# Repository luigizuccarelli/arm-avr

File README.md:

# arm-avr

## Arm 0 based on the LPC11U37FBD64-501 32bit mcu

 * **Design**
   * All pcb and schematics are in Kicad format
   * Double sided through hole plated pcb
   * Not in production yet waiting for pcb's to be manufactured for QA testing

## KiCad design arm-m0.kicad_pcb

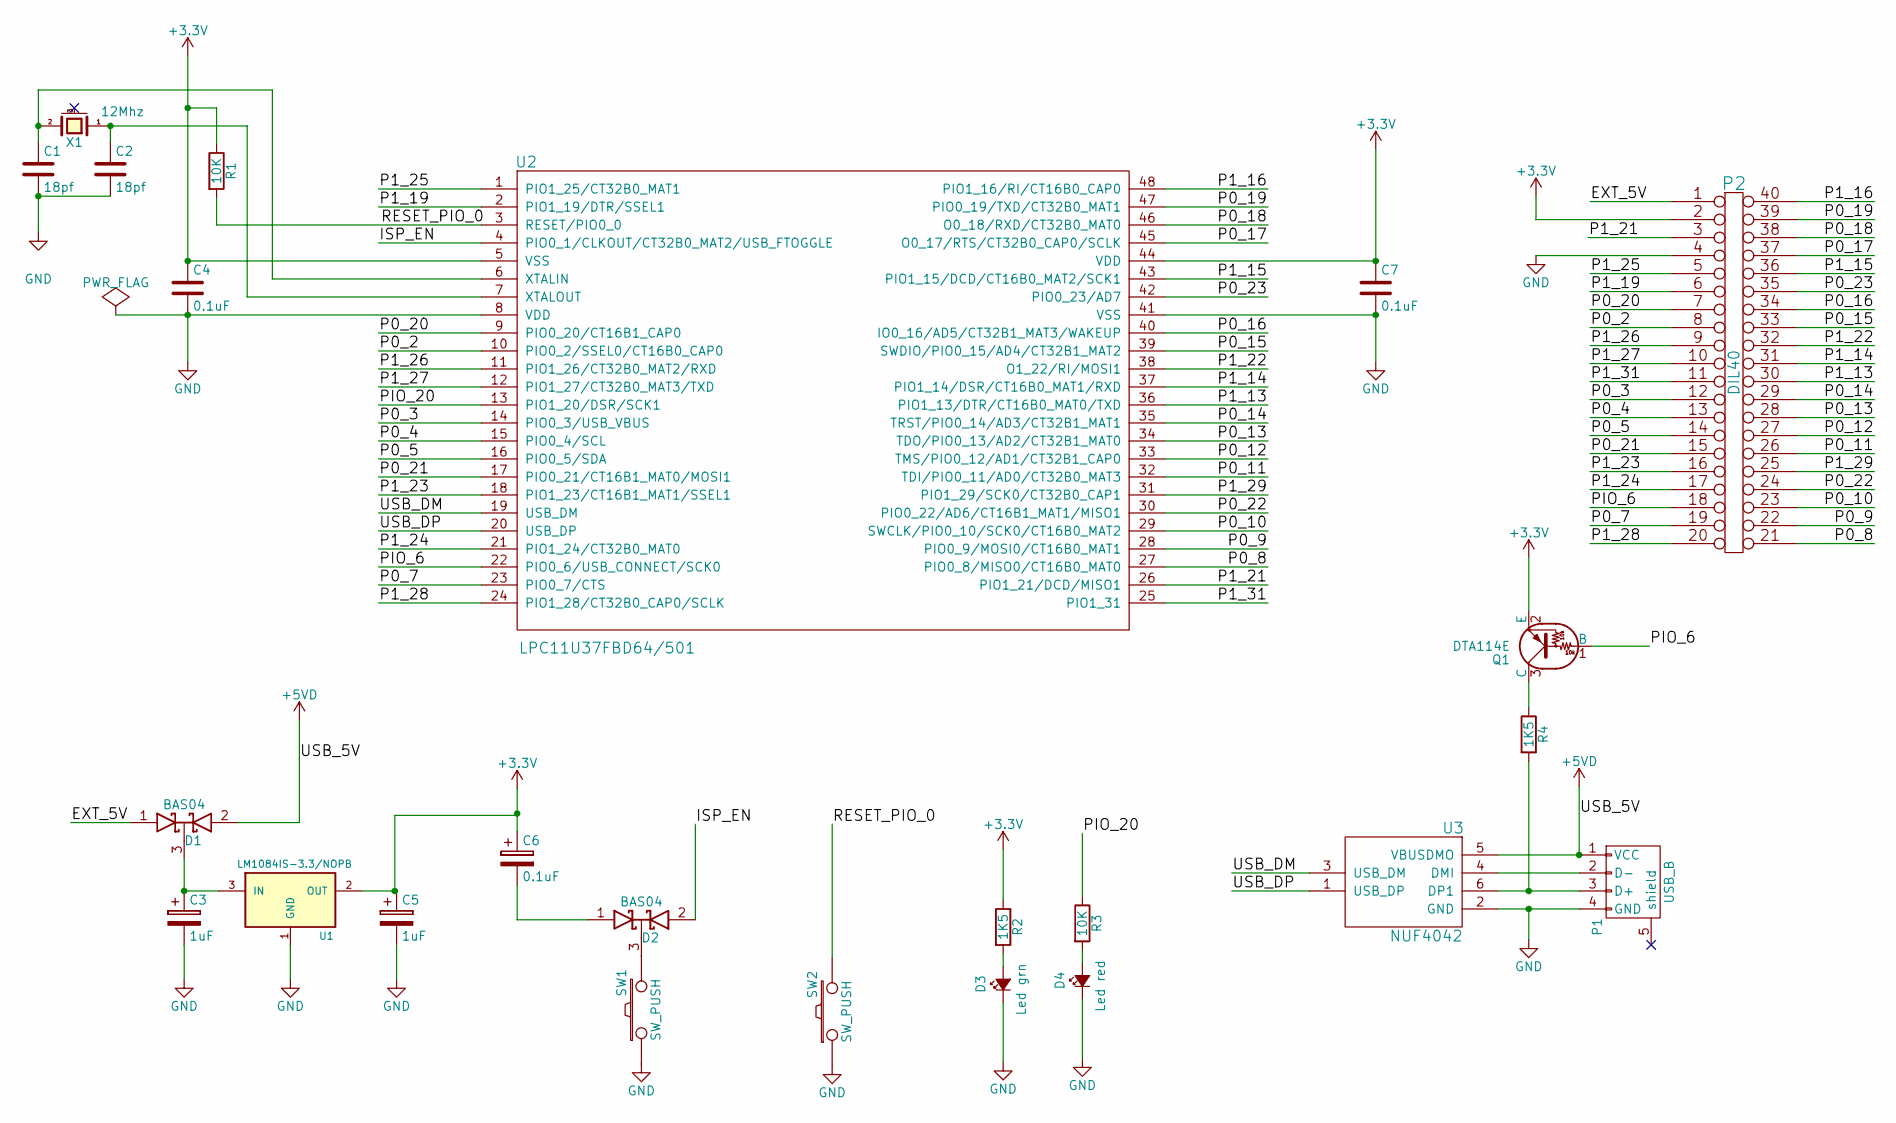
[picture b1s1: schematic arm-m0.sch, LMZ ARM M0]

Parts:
C1, C2: 18pf; C_0402
C3, C5: 1uF; R_0603_HandSoldering
C4, C6, C7: 0.1uF; R_0603_HandSoldering
D1, D2: BAS04; SOT-23
D3: Led grn; LED-0805
D4: Led red; LED-0805
P1: USB_B; USB_Micro-B
P2: DIL40; DIP-40_W25.4mm
Q1: DTA114E; SOT-23
R1: 10K; R_0603
R2, R4: 1K5; R_0603_HandSoldering
R3: 10K; R_0603_HandSoldering
SW1, SW2: SW_PUSH; SW_PUSH_SMALL
U1: LM1084IS-3.3/NOPB; SOT-23
U2: LPC11U37FBD64/501; LQFP-48_7x7mm_Pitch0.5mm
U3: NUF4042; SOT-563
X1: 12Mhz; Crystal_SMD_0603_4Pads

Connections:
+3V3: C4.1, C5.1, C6.1, C7.1, P2.2, Q1.2 (E), R1.1, R2.1, U1.2 (OUT), U2.5 (VSS), U2.44 (VDD)
+5VD: D1.2 (A), P1.1 (VCC), U3.5 (VBUSDMO)
/EXT_5V: D1.1 (A), P2.1
/ISP_EN: D2.2 (A), U2.4 (PIO0_1/CLKOUT/CT32B0_MAT2/USB_FTOGGLE)
/P0_2: P2.8, U2.10 (PIO0_2/SSEL0/CT16B0_CAP0)
/P0_3: P2.12, U2.14 (PIO0_3/USB_VBUS)
/P0_4: P2.13, U2.15 (PIO0_4/SCL)
/P0_5: P2.14, U2.16 (PIO0_5/SDA)
/P0_7: P2.19, U2.23 (PIO0_7/CTS)
/P0_8: P2.21, U2.27 (PIO0_8/MISO0/CT16B0_MAT0)
/P0_9: P2.22, U2.28 (PIO0_9/MOSI0/CT16B0_MAT1)
/P0_10: P2.23, U2.29 (SWCLK/PIO0_10/SCK0/CT16B0_MAT2)
/P0_11: P2.26, U2.32 (TDI/PIO0_11/AD0/CT32B0_MAT3)
/P0_12: P2.27, U2.33 (TMS/PIO0_12/AD1/CT32B1_CAP0)
/P0_13: P2.28, U2.34 (TDO/PIO0_13/AD2/CT32B1_MAT0)
/P0_14: P2.29, U2.35 (TRST/PIO0_14/AD3/CT32B1_MAT1)
/P0_15: P2.33, U2.39 (SWDIO/PIO0_15/AD4/CT32B1_MAT2)
/P0_16: P2.34, U2.40 (IO0_16/AD5/CT32B1_MAT3/WAKEUP)
/P0_17: P2.37, U2.45 (O0_17/RTS/CT32B0_CAP0/SCLK)
/P0_18: P2.38, U2.46 (O0_18/RXD/CT32B0_MAT0)
/P0_19: P2.39, U2.47 (PIO0_19/TXD/CT32B0_MAT1)
/P0_20: P2.7, U2.9 (PIO0_20/CT16B1_CAP0)
/P0_21: P2.15, U2.17 (PIO0_21/CT16B1_MAT0/MOSI1)
/P0_22: P2.24, U2.30 (PIO0_22/AD6/CT16B1_MAT1/MISO1)
/P0_23: P2.35, U2.42 (PIO0_23/AD7)
/P1_13: P2.30, U2.36 (PIO1_13/DTR/CT16B0_MAT0/TXD)
/P1_14: P2.31, U2.37 (PIO1_14/DSR/CT16B0_MAT1/RXD)
/P1_15: P2.36, U2.43 (PIO1_15/DCD/CT16B0_MAT2/SCK1)
/P1_16: P2.40, U2.48 (PIO1_16/RI/CT16B0_CAP0)
/P1_19: P2.6, U2.2 (PIO1_19/DTR/SSEL1)
/P1_21: P2.3, U2.26 (PIO1_21/DCD/MISO1)
/P1_22: P2.32, U2.38 (O1_22/RI/MOSI1)
/P1_23: P2.16, U2.18 (PIO1_23/CT16B1_MAT1/SSEL1)
/P1_24: P2.17, U2.21 (PIO1_24/CT32B0_MAT0)
/P1_25: P2.5, U2.1 (PIO1_25/CT32B0_MAT1)
/P1_26: P2.9, U2.11 (PIO1_26/CT32B0_MAT2/RXD)
/P1_27: P2.10, U2.12 (PIO1_27/CT32B0_MAT3/TXD)
/P1_28: P2.20, U2.24 (PIO1_28/CT32B0_CAP0/SCLK)
/P1_29: P2.25, U2.31 (PIO1_29/SCK0/CT32B0_CAP1)
/P1_31: P2.11, U2.25 (PIO1_31)
/PIO_6: P2.18, Q1.1 (B), U2.22 (PIO0_6/USB_CONNECT/SCK0)
/PIO_20: R3.1, U2.13 (PIO1_20/DSR/SCK1)
/RESET_PIO_0: R1.2, SW2.2, U2.3 (RESET/PIO0_0)
/USB_DM: U2.19 (USB_DM), U3.3 (USB_DM)
/USB_DP: U2.20 (USB_DP), U3.1 (USB_DP)
GND: C1.2, C2.2, C3.2, C4.2, C5.2, C7.2, D3.1 (K), D4.1 (K), P1.4 (GND), P2.4, SW1.1, SW2.1, U1.1 (GND), U2.8 (VDD), U2.41 (VSS), U3.2 (GND)
unnamed: C1.1, U2.6 (XTALIN), X1.2
unnamed: C2.1, U2.7 (XTALOUT), X1.1
unnamed: C3.1, D1.3 (K), U1.3 (IN)
unnamed: C6.2, D2.1 (A)
unnamed: D2.3 (K), SW1.2
unnamed: D3.2 (A), R2.2
unnamed: D4.2 (A), R3.2
unnamed: P1.2 (D-), U3.4 (DMI)
unnamed: P1.3 (D+), R4.2, U3.6 (DP1)
unnamed: Q1.3 (C), R4.1

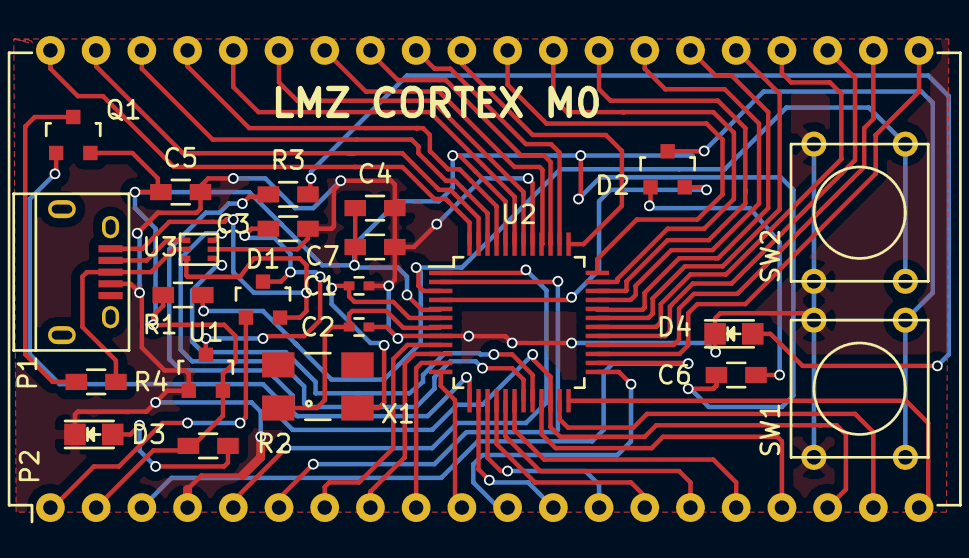
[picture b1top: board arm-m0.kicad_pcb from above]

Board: 2 copper layers, 24 parts (0 on the bottom side), 56 nets.

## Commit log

2016-03-31 Added pcb and scematic design files
